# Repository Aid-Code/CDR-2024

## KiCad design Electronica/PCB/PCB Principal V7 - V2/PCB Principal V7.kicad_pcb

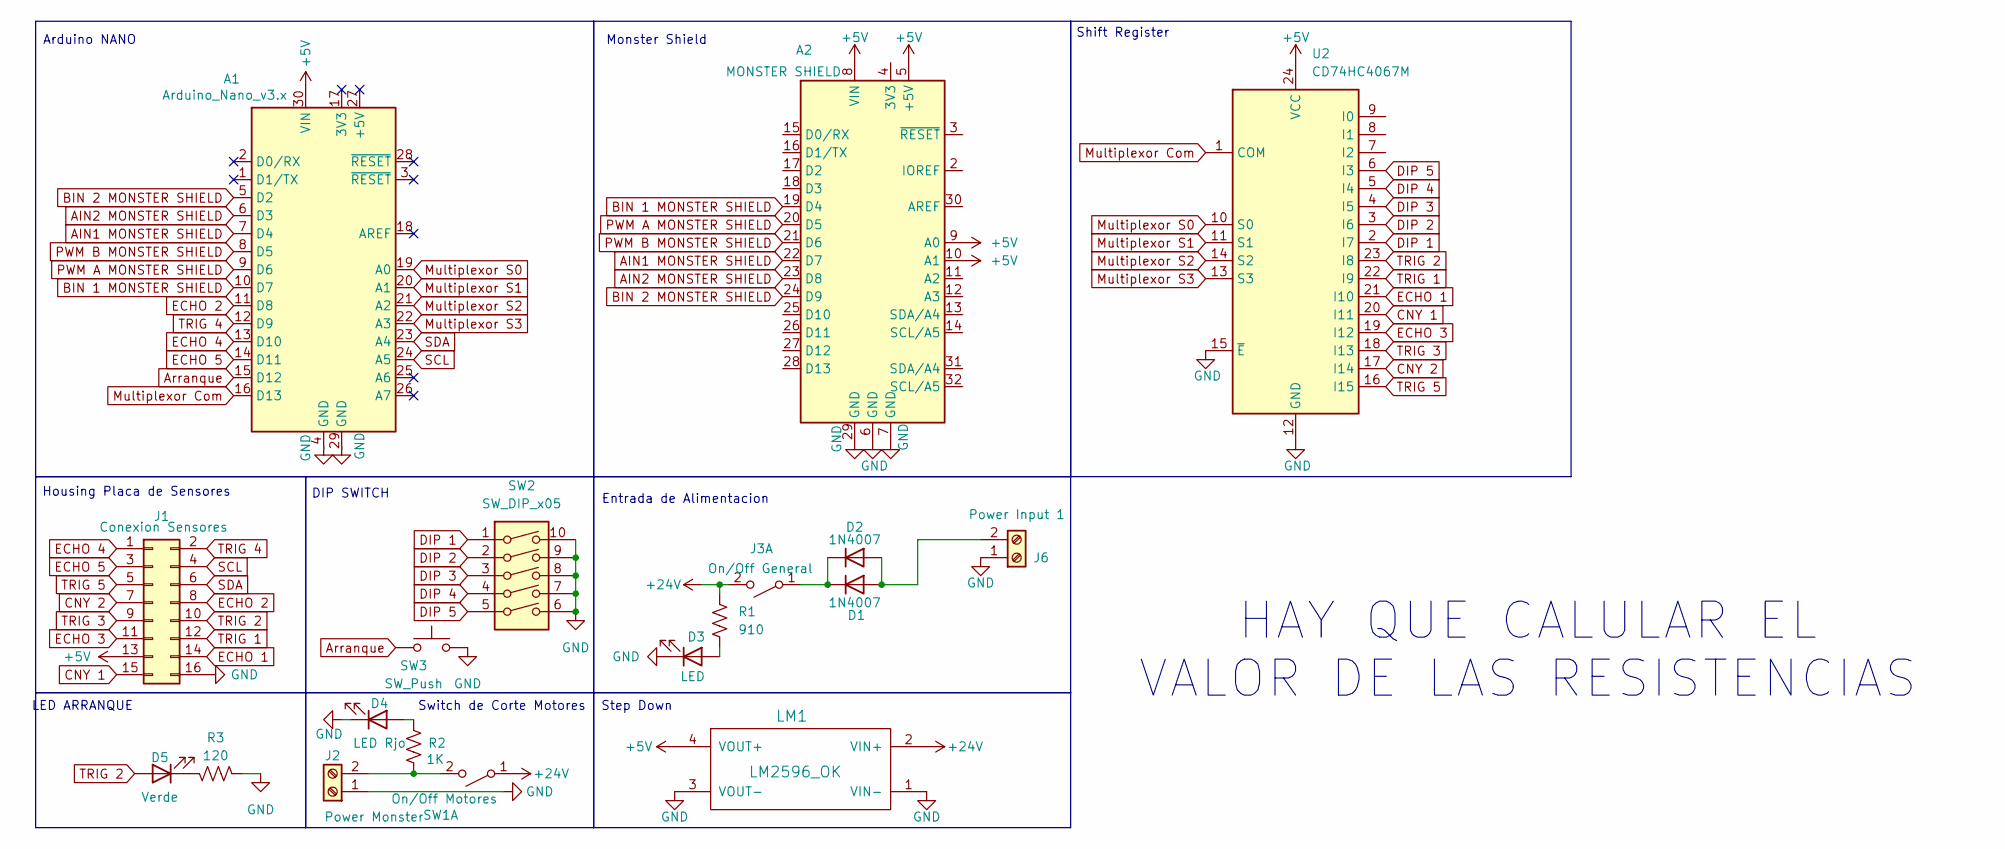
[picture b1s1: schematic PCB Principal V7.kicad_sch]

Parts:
A1: Arduino_Nano_v3.x; Arduino_Nano
A2: MONSTER SHIELD; Arduino_UNO_R3
D1, D2: 1N4007; D_DO-41_SOD81_P10.16mm_Horizontal
D3: LED; LED_D5.0mm_Horizontal_O1.27mm_Z3.0mm
D4: LED Rjo; LED_D5.0mm_Horizontal_O1.27mm_Z3.0mm
D5: Verde; LED_D5.0mm_Clear
J1: Conexion Sensores; PinHeader_2x08_P2.54mm_Horizontal
J2: Power Monster; TerminalBlock_bornier-2_P5.08mm
J3: On/Off General; TerminalBlock_bornier-2_P5.08mm
J6: Power Input 1; AMASS_XT60-M_1x02_P7.20mm_Vertical
LM1: LM2596_OK; StepDown
R1: 910; R_Axial_DIN0204_L3.6mm_D1.6mm_P7.62mm_Horizontal
R2: 1K; R_Axial_DIN0204_L3.6mm_D1.6mm_P7.62mm_Horizontal
R3: 120; R_Axial_DIN0204_L3.6mm_D1.6mm_P7.62mm_Horizontal
SW1: On/Off Motores; SW_Slide_SPDT_Angled_CK_OS102011MA1Q
SW2: SW_DIP_x05; SW_DIP_SPSTx05_Slide_9.78x14.88mm_W7.62mm_P2.54mm
SW3: SW_Push; SW_PUSH_6mm
U2: CD74HC4067M; SOIC-24W_7.5x15.4mm_P1.27mm

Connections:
+5V: A1.30 (VIN), A2.5 (+5V), A2.8 (VIN), A2.9 (A0), A2.10 (A1), J1.13, LM1.4 (VOUT+), U2.24 (VCC)
+24V: J3.2 (B), LM1.2 (VIN+), R1.1, SW1.1 (A)
AIN1 MONSTER SHIELD: A1.7 (D4), A2.22 (D7)
AIN2 MONSTER SHIELD: A1.6 (D3), A2.23 (D8)
Arranque: A1.15 (D12), SW3.1
BIN 1 MONSTER SHIELD: A1.10 (D7), A2.19 (D4)
BIN 2 MONSTER SHIELD: A1.5 (D2), A2.24 (D9)
CNY 1: J1.15, U2.20 (I11)
CNY 2: J1.7, U2.17 (I14)
DIP 1: SW2.1, U2.2 (I7)
DIP 2: SW2.2, U2.3 (I6)
DIP 3: SW2.3, U2.4 (I5)
DIP 4: SW2.4, U2.5 (I4)
DIP 5: SW2.5, U2.6 (I3)
ECHO 1: J1.14, U2.21 (I10)
ECHO 2: A1.11 (D8), J1.8
ECHO 3: J1.11, U2.19 (I12)
ECHO 4: A1.13 (D10), J1.1
ECHO 5: A1.14 (D11), J1.3
GND: A1.4 (GND), A1.29 (GND), A2.6 (GND), A2.7 (GND), A2.29 (GND), D3.1 (K), D4.1 (K), J1.16, J2.1, J6.1, LM1.1 (VIN-), LM1.3 (VOUT-), R3.2, SW2.6, SW2.7, SW2.8, SW2.9, SW2.10, SW3.2, U2.12 (GND), U2.15 (~E)
Multiplexor Com: A1.16 (D13), U2.1 (COM)
Multiplexor S0: A1.19 (A0), U2.10 (S0)
Multiplexor S1: A1.20 (A1), U2.11 (S1)
Multiplexor S2: A1.21 (A2), U2.14 (S2)
Multiplexor S3: A1.22 (A3), U2.13 (S3)
unnamed: D1.2 (A), D2.2 (A), J6.2
unnamed: D1.1 (K), D2.1 (K), J3.1 (A)
unnamed: D3.2 (A), R1.2
unnamed: D4.2 (A), R2.2
unnamed: D5.1 (K), R3.1
unnamed: J2.2, R2.1, SW1.2 (B)
PWM A MONSTER SHIELD: A1.9 (D6), A2.20 (D5)
PWM B MONSTER SHIELD: A1.8 (D5), A2.21 (D6)
SCL: A1.24 (A5), J1.4
SDA: A1.23 (A4), J1.6
TRIG 1: J1.12, U2.22 (I9)
TRIG 2: D5.2 (A), J1.10, U2.23 (I8)
TRIG 3: J1.9, U2.18 (I13)
TRIG 4: A1.12 (D9), J1.2
TRIG 5: J1.5, U2.16 (I15)

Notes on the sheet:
Switch de Corte Motores
Entrada de Alimentacion
Shift Register
LED ARRANQUE
Step Down
Housing Placa de Sensores
HAY QUE CALULAR EL VALOR DE LAS RESISTENCIAS
Monster Shield
Arduino NANO
DIP SWITCH

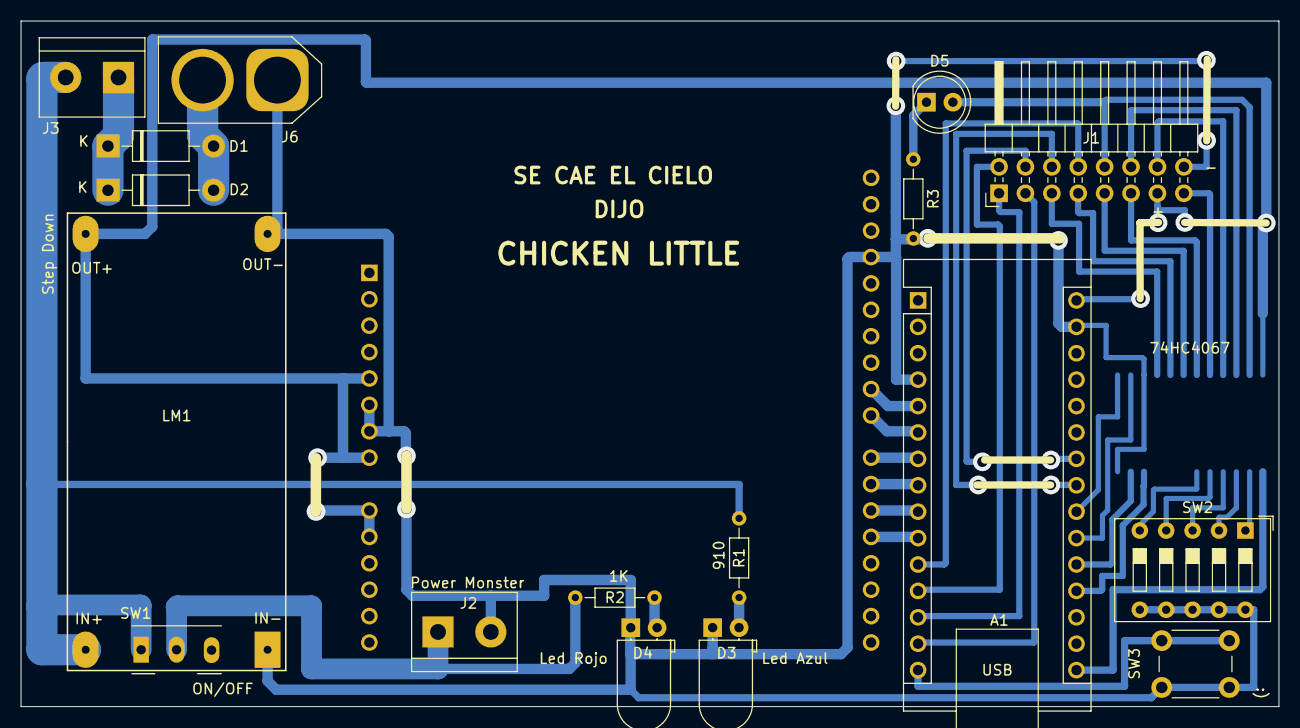
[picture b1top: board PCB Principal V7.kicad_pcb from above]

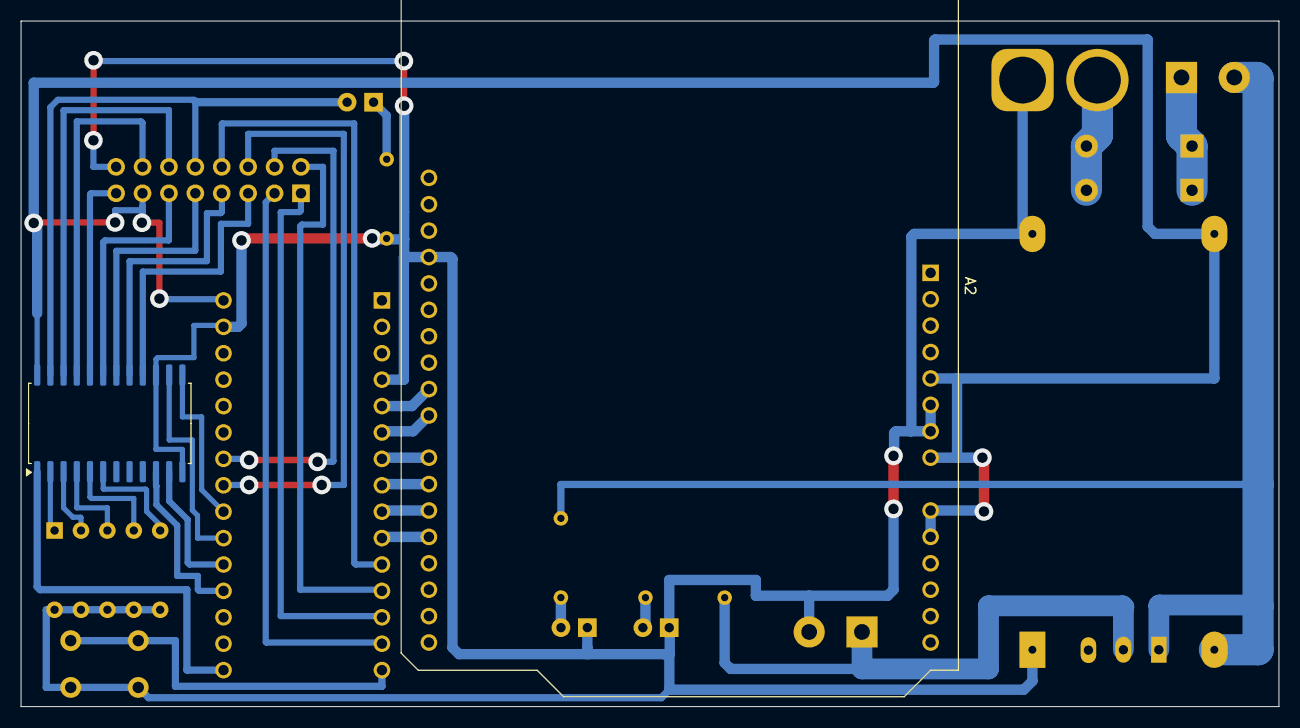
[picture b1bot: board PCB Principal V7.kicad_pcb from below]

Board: 2 copper layers, 121.0 x 65.9 mm, 19 parts (2 on the bottom side), 40 nets.

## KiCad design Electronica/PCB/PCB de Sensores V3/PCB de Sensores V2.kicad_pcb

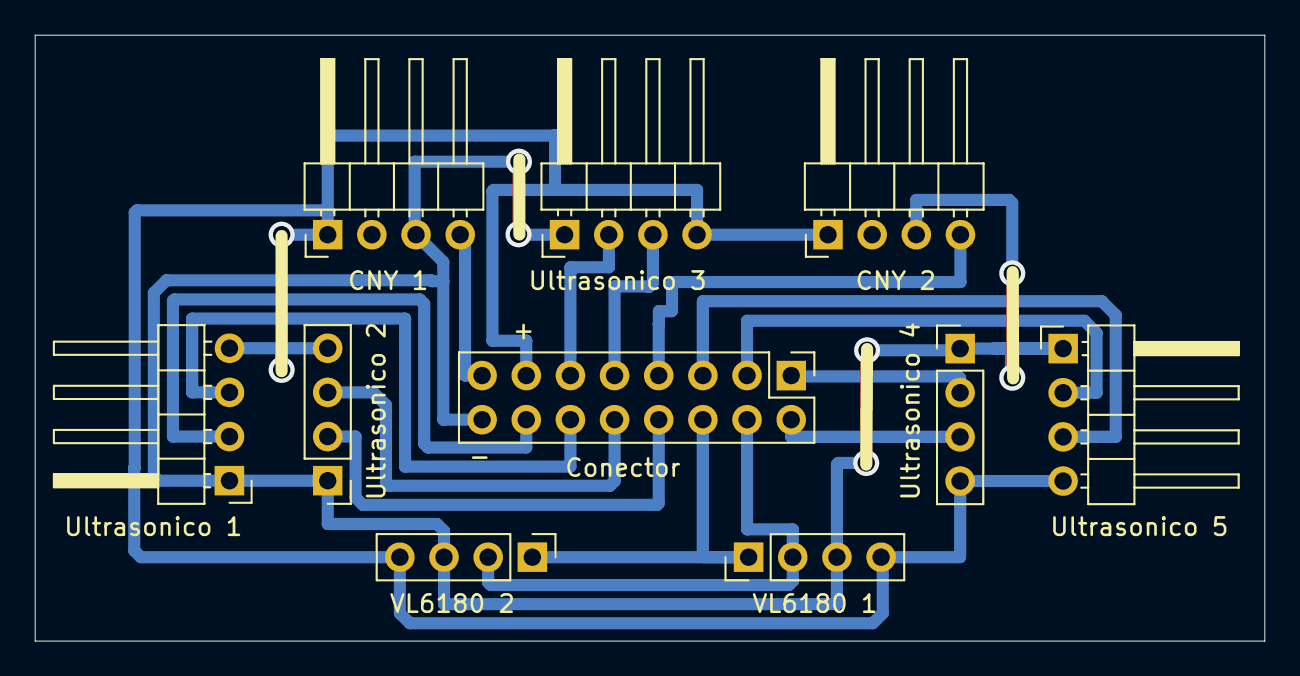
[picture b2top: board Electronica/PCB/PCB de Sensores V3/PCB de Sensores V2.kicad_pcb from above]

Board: 2 copper layers, 70.7 x 34.9 mm, 10 parts (0 on the bottom side), 16 nets.

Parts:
CNY 1: CNY1; PinHeader_1x04_P2.54mm_Horizontal
CNY 2: CNY2; PinHeader_1x04_P2.54mm_Horizontal
Conector: Conexion Sensores; PinHeader_2x08_P2.54mm_Vertical
Ultrasonico 1: ULTRASONICO1; PinHeader_1x04_P2.54mm_Horizontal
Ultrasonico 2: ULTRASONICO2; PinHeader_1x04_P2.54mm_Vertical
Ultrasonico 3: ULTRASONICO3; PinHeader_1x04_P2.54mm_Horizontal
Ultrasonico 4: ULTRASONICO4; PinHeader_1x04_P2.54mm_Vertical
Ultrasonico 5: ULTRASONICO5; PinHeader_1x04_P2.54mm_Horizontal
VL6180 1: VL6180 1; PinHeader_1x04_P2.54mm_Vertical
VL6180 2: VL6180 2; PinHeader_1x04_P2.54mm_Vertical

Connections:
+5V: CNY 1.1, CNY 2.1, Conector.13, Ultrasonico 1.4, Ultrasonico 2.4, Ultrasonico 3.4, Ultrasonico 4.4, Ultrasonico 5.4, VL6180 1.4, VL6180 2.4
CNY 1: CNY 1.4, Conector.15
CNY 2: CNY 2.4, Conector.7
ECHO 1: Conector.14, Ultrasonico 1.2
ECHO 2: Conector.8, Ultrasonico 2.2
ECHO 3: Conector.11, Ultrasonico 3.2
ECHO 4: Conector.1, Ultrasonico 4.2
ECHO 5: Conector.3, Ultrasonico 5.2
GND: CNY 1.3, CNY 2.3, Conector.16, Ultrasonico 1.1, Ultrasonico 2.1, Ultrasonico 3.1, Ultrasonico 4.1, Ultrasonico 5.1, VL6180 1.3, VL6180 2.3
SCL: Conector.4, VL6180 1.2, VL6180 2.2
SDA: Conector.6, VL6180 1.1, VL6180 2.1
TRIG 1: Conector.12, Ultrasonico 1.3
TRIG 2: Conector.10, Ultrasonico 2.3
TRIG 3: Conector.9, Ultrasonico 3.3
TRIG 4: Conector.2, Ultrasonico 4.3
TRIG 5: Conector.5, Ultrasonico 5.3

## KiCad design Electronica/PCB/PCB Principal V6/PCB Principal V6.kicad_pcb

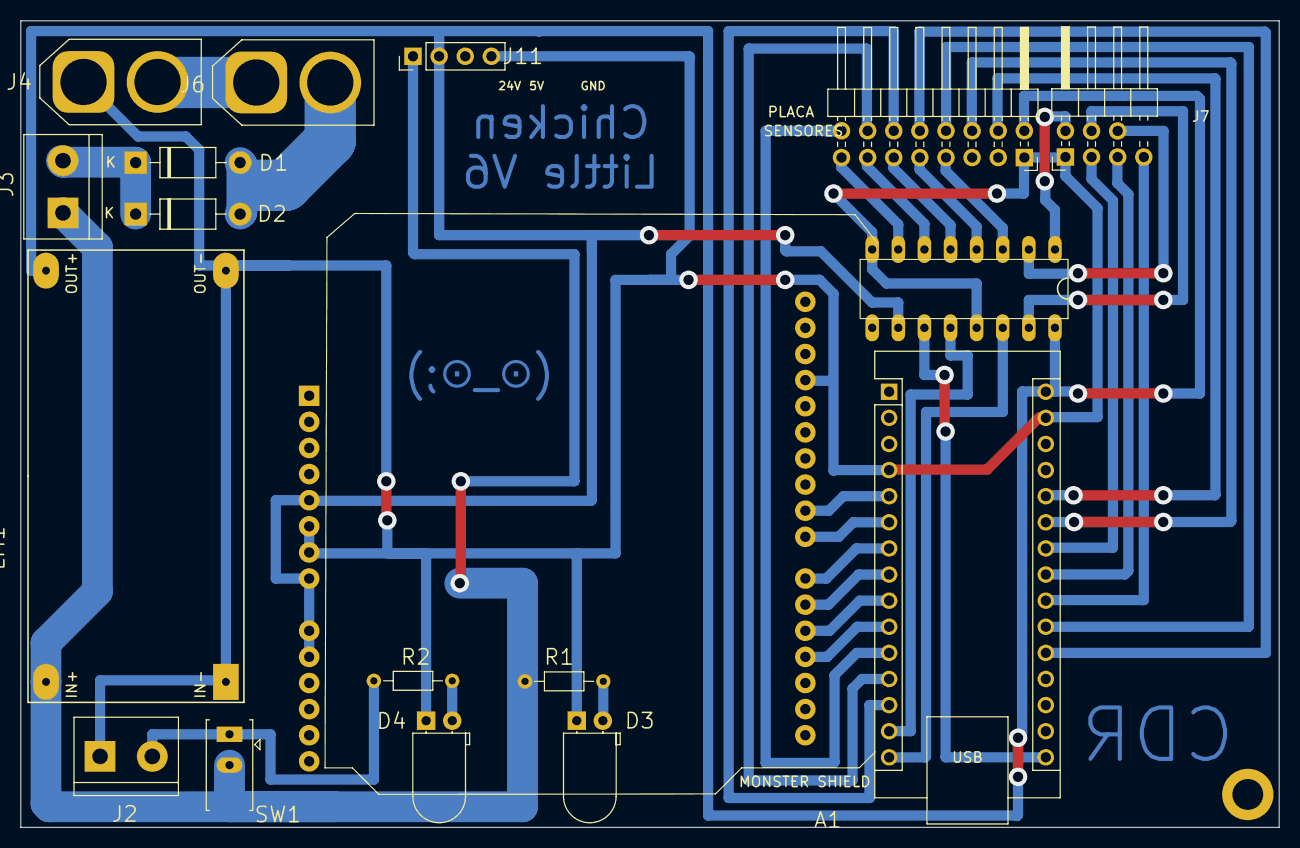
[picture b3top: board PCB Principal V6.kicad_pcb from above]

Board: 2 copper layers, 122.4 x 78.4 mm, 18 parts (1 on the bottom side), 36 nets.

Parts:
A1: Arduino_Nano_v3.x; Arduino_Nano
A2: MONSTER SHIELD; Arduino_UNO_R3
D1, D2: 1N4007; D_DO-41_SOD81_P10.16mm_Horizontal
D3, D4: LED; LED_D5.0mm_Horizontal_O1.27mm_Z3.0mm
J1: Conexion Sensores; PinHeader_2x08_P2.54mm_Horizontal
J2: Power Monster; TerminalBlock_bornier-2_P5.08mm
J3: On/Off General; TerminalBlock_bornier-2_P5.08mm
J4: Power Input 2; AMASS_XT60-M_1x02_P7.20mm_Vertical
J6: Power Input 1; AMASS_XT60-M_1x02_P7.20mm_Vertical
J7: Placa de Botones; PinHeader_2x04_P2.54mm_Horizontal
J11: Conn_01x04_Pin; PinHeader_1x04_P2.54mm_Vertical
LM1: LM2596_OK; StepDown
R1, R2: 220; R_Axial_DIN0204_L3.6mm_D1.6mm_P7.62mm_Horizontal
SW1: On/Off Motores; SW_Slide_SPDT_Straight_CK_OS102011MS2Q
U1: 74HC595; DIP16-2.54-20.32X5.84MM

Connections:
+5V: A1.30 (VIN), A2.5 (+5V), A2.8 (VIN), A2.9 (A0), A2.10 (A1), J1.15, J11.2, LM1.4 (VOUT+), U1.10 (~SRCLR), U1.16 (VCC)
+24V: J3.1 (A), J11.1, LM1.2 (VIN+), R1.1, SW1.2 (B)
AIN1 MONSTER SHIELD: A1.7 (D4), A2.22 (D7)
AIN2 MONSTER SHIELD: A1.6 (D3), A2.23 (D8)
BIN 1 MONSTER SHIELD: A1.10 (D7), A2.19 (D4)
BIN 2 MONSTER SHIELD: A1.5 (D2), A2.24 (D9)
BTN1: A1.23 (A4), J7.5
BTN2: A1.24 (A5), J7.3
CNY 1: A1.26 (A7), J1.13
CNY 2: A1.25 (A6), J1.11
Clock: A1.16 (D13), U1.11 (SRCLK)
Data: A1.15 (D12), U1.14 (SER)
ECHO 1: A1.11 (D8), J1.1
ECHO 2: A1.12 (D9), J1.3
ECHO 3: A1.13 (D10), J1.5
ECHO 4: A1.20 (A1), J1.7
ECHO 5: A1.21 (A2), J1.9
GND: A1.4 (GND), A1.29 (GND), A2.6 (GND), A2.7 (GND), A2.29 (GND), D3.1 (K), D4.1 (K), J1.16, J2.1, J4.1, J7.1, J11.4, LM1.1 (VIN-), LM1.3 (VOUT-), U1.8 (GND), U1.13 (~OE)
LED1: A1.22 (A3), J7.7
LED2: J7.2, U1.1 (QB)
LED3: J7.4, U1.15 (QA)
LED4: J7.6, U1.2 (QC)
Latch: A1.14 (D11), U1.12 (RCLK)
unnamed: D1.2 (A), D2.2 (A), J6.2
unnamed: D1.1 (K), D2.1 (K), J3.2 (B)
unnamed: D3.2 (A), R1.2
unnamed: D4.2 (A), R2.2
unnamed: J2.2, R2.1, SW1.1 (A)
unnamed: J4.2, J6.1
PWM A MONSTER SHIELD: A1.9 (D6), A2.20 (D5)
PWM B MONSTER SHIELD: A1.8 (D5), A2.21 (D6)
TRIG 1: J1.10, U1.3 (QD)
TRIG 2: J1.2, U1.7 (QH)
TRIG 3: J1.4, U1.6 (QG)
TRIG 4: J1.8, U1.4 (QE)
TRIG 5: J1.6, U1.5 (QF)

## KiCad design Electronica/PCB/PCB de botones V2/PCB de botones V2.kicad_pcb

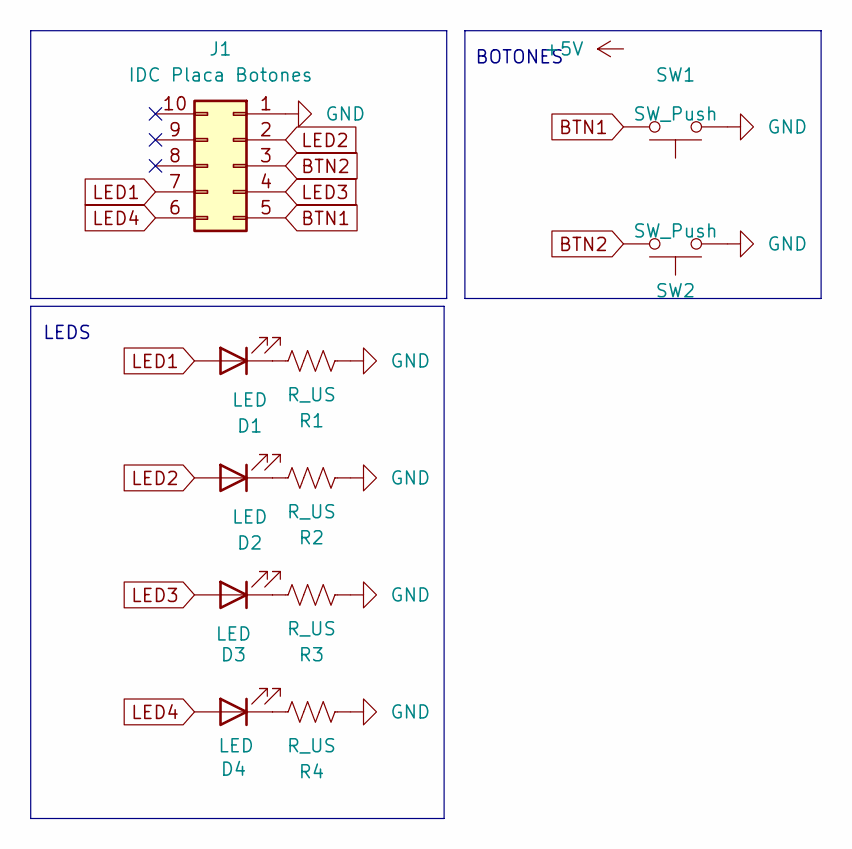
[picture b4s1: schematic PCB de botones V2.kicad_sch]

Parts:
D1, D2, D3, D4: LED; LED_D5.0mm
J1: IDC Placa Botones; IDC-Header_2x05_P2.54mm_Horizontal
R1, R2, R3, R4: R_US; R_Axial_DIN0207_L6.3mm_D2.5mm_P10.16mm_Horizontal
SW1, SW2: SW_Push; SW_PUSH_6mm

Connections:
BTN1: J1.5, SW1.1
BTN2: J1.3, SW2.1
GND: J1.1, R1.1, R2.1, R3.1, R4.1, SW1.2, SW2.2
LED1: D1.2 (A), J1.7
LED2: D2.2 (A), J1.2
LED3: D3.2 (A), J1.4
LED4: D4.2 (A), J1.6
unnamed: D1.1 (K), R1.2
unnamed: D2.1 (K), R2.2
unnamed: D3.1 (K), R3.2
unnamed: D4.1 (K), R4.2

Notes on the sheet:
LEDS
BOTONES

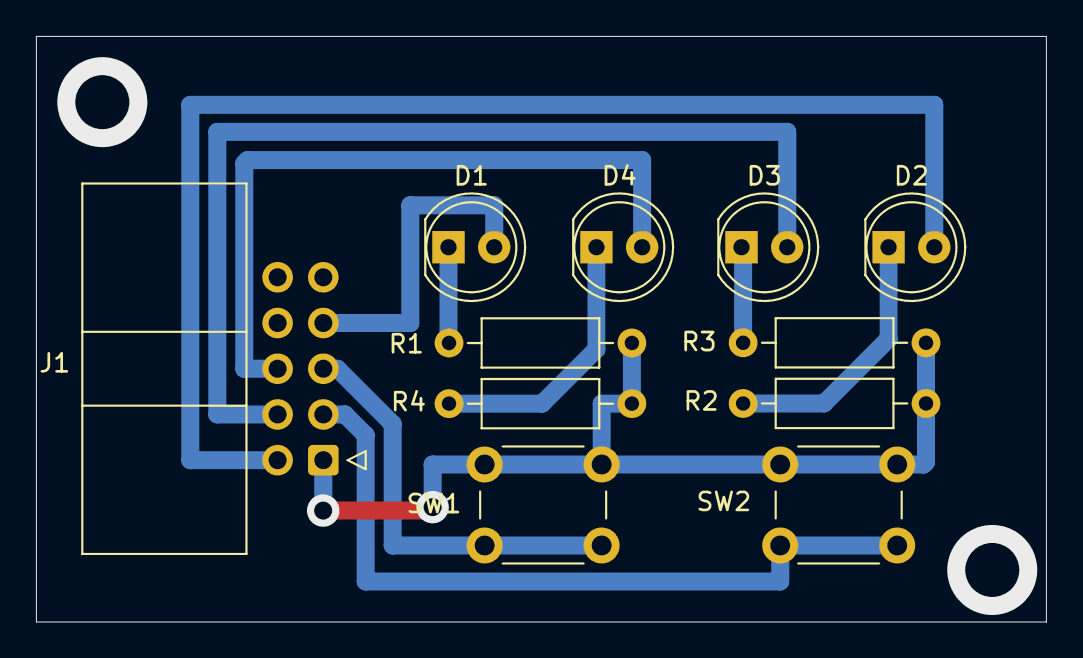
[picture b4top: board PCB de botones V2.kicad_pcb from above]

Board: 2 copper layers, 56.1 x 32.5 mm, 11 parts (0 on the bottom side), 11 nets.

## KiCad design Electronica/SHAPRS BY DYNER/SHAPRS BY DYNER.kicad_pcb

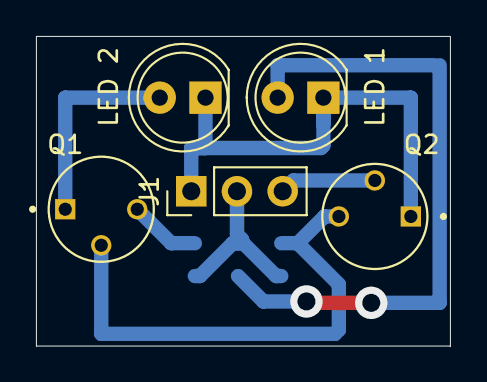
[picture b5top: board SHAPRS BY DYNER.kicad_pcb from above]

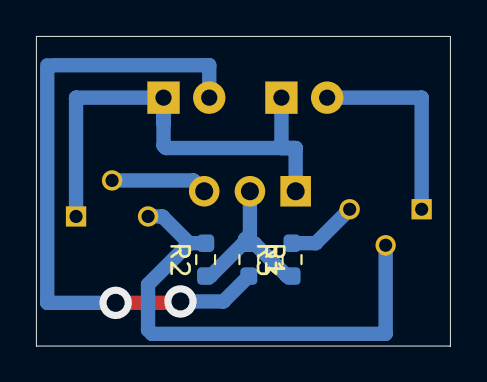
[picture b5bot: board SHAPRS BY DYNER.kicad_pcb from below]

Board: 2 copper layers, 23.0 x 17.2 mm, 8 parts (3 on the bottom side), 7 nets.

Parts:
J1: Conn_01x03_Socket; PinHeader_1x03_P2.54mm_Vertical
LED 1, LED 2: LED; LED_D5.0mm
Q1, Q2: 2N2222A; TO127P584H533-3
R1, R2, R3: 330; R_0603_1608Metric_Pad0.98x0.95mm_HandSolder

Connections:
+5V: J1.2, R1.1, R2.1, R3.1
GND: J1.1, LED 1.1 (K), LED 2.1 (K), Q2.1
unnamed: LED 1.2 (A), R1.2
unnamed: LED 2.2 (A), Q1.1
unnamed: Q1.2, Q2.3, R2.2
unnamed: Q1.3, R3.2
pin: J1.3, Q2.2

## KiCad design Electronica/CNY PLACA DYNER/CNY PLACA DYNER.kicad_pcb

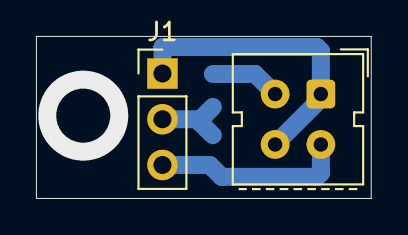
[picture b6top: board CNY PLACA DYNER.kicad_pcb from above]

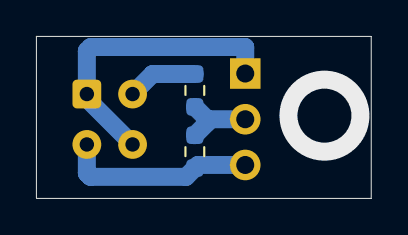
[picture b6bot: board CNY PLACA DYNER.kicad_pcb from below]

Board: 2 copper layers, 18.6 x 9.0 mm, 4 parts (2 on the bottom side), 4 nets.

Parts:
J1: Conn_01x03_Socket; PinHeader_1x03_P2.54mm_Vertical
R1: 220; R_0603_1608Metric_Pad0.98x0.95mm_HandSolder
R2: 10k; R_0603_1608Metric_Pad0.98x0.95mm_HandSolder
U1: CNY70; Vishay_CNY70

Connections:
+5V: J1.1, U1.1 (A), U1.3 (C)
CNY: J1.3, R2.1, U1.4 (E)
GND: J1.2, R1.1, R2.2
unnamed: R1.2, U1.2 (K)

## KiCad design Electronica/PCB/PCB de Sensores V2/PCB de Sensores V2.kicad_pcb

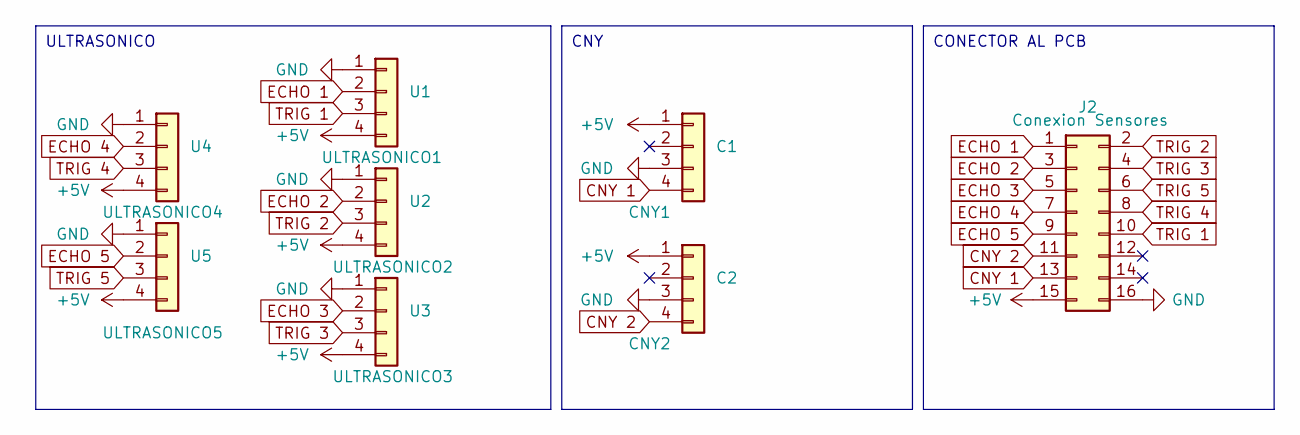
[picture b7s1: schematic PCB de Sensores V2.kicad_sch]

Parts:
C1: CNY1; PinHeader_1x04_P2.54mm_Horizontal
C2: CNY2; PinHeader_1x04_P2.54mm_Horizontal
J2: Conexion Sensores; PinHeader_2x08_P2.54mm_Vertical
U1: ULTRASONICO1; PinHeader_1x04_P2.54mm_Horizontal
U2: ULTRASONICO2; PinHeader_1x04_P2.54mm_Vertical
U3: ULTRASONICO3; PinHeader_1x04_P2.54mm_Horizontal
U4: ULTRASONICO4; PinHeader_1x04_P2.54mm_Vertical
U5: ULTRASONICO5; PinHeader_1x04_P2.54mm_Horizontal

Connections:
+5V: C1.1, C2.1, J2.15, U1.4, U2.4, U3.4, U4.4, U5.4
CNY 1: C1.4, J2.13
CNY 2: C2.4, J2.11
ECHO 1: J2.1, U1.2
ECHO 2: J2.3, U2.2
ECHO 3: J2.5, U3.2
ECHO 4: J2.7, U4.2
ECHO 5: J2.9, U5.2
GND: C1.3, C2.3, J2.16, U1.1, U2.1, U3.1, U4.1, U5.1
TRIG 1: J2.10, U1.3
TRIG 2: J2.2, U2.3
TRIG 3: J2.4, U3.3
TRIG 4: J2.8, U4.3
TRIG 5: J2.6, U5.3

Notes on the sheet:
CONECTOR AL PCB
ULTRASONICO
CNY

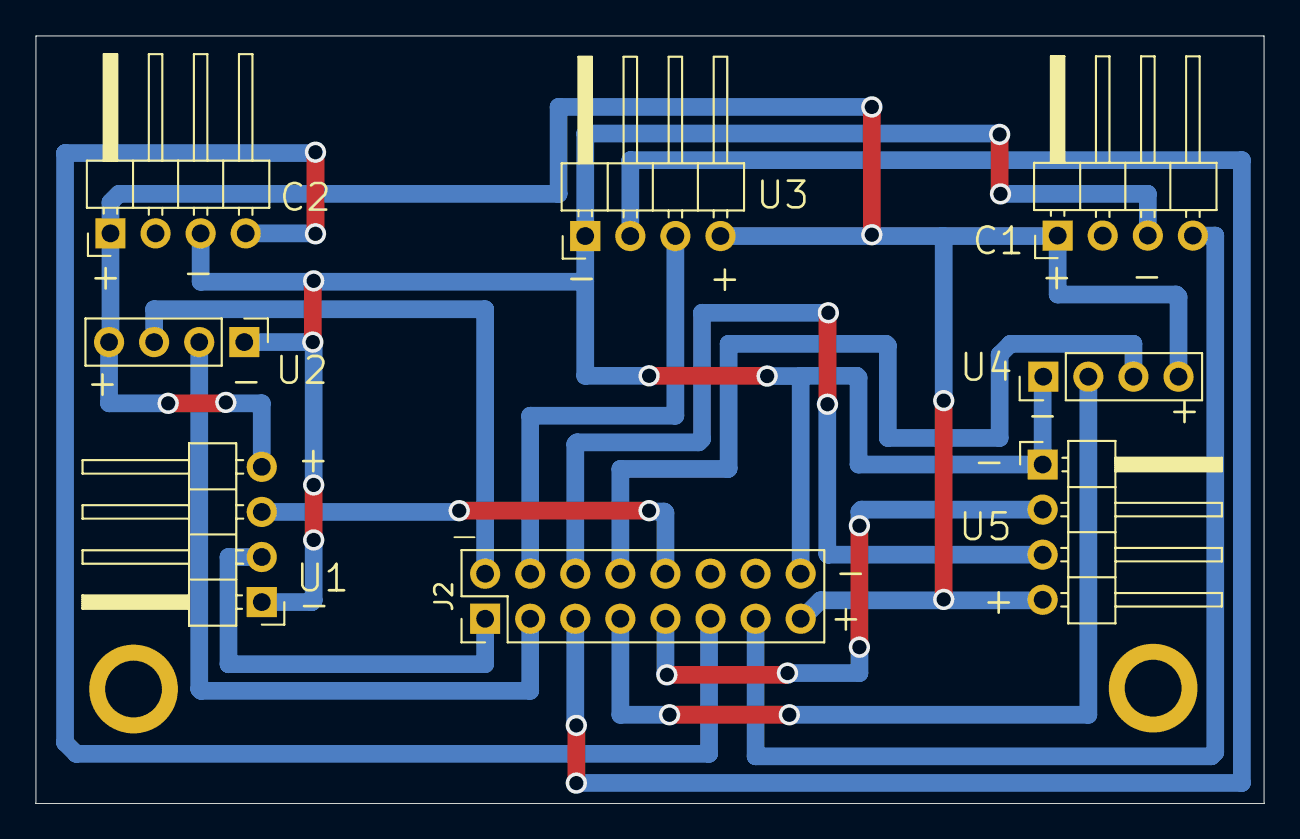
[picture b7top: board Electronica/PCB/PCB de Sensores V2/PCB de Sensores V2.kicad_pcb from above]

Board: 2 copper layers, 69.2 x 43.3 mm, 8 parts (0 on the bottom side), 14 nets.

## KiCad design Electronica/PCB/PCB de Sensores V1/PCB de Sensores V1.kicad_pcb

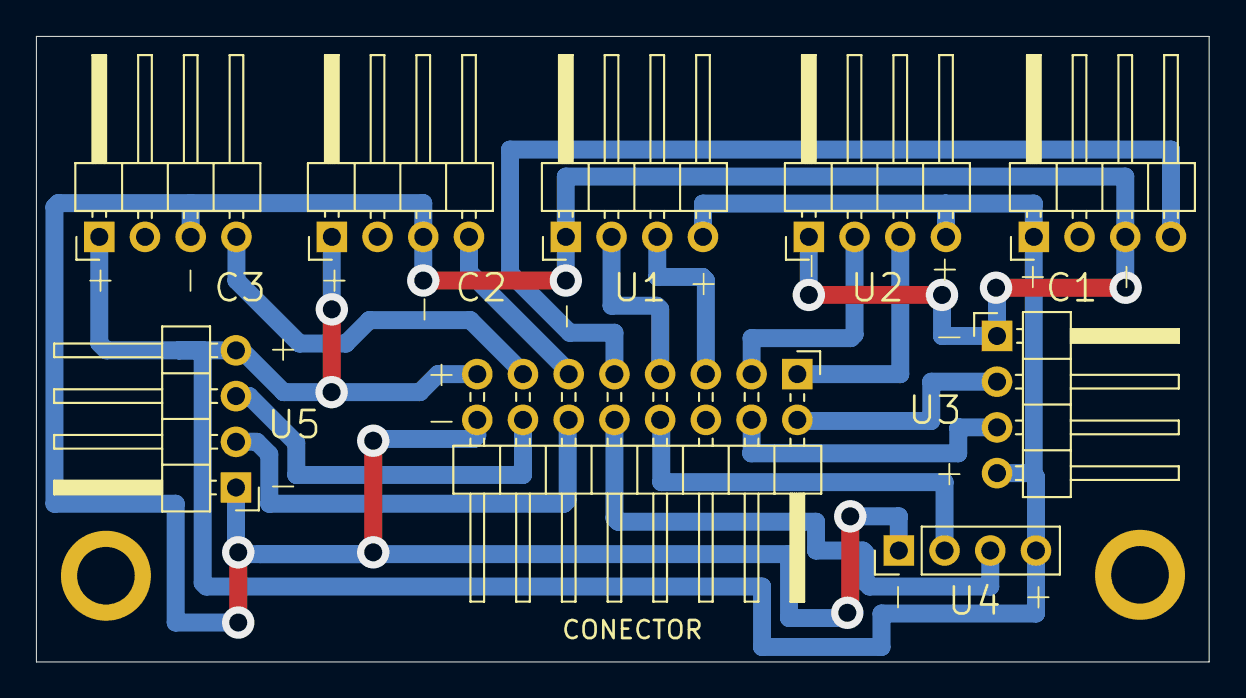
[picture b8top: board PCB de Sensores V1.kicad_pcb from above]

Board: 2 copper layers, 65.2 x 34.7 mm, 9 parts (0 on the bottom side), 15 nets.

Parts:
C1: CNY1; PinHeader_1x04_P2.54mm_Horizontal
C2: CNY2; PinHeader_1x04_P2.54mm_Horizontal
C3: CNY3; PinHeader_1x04_P2.54mm_Horizontal
CONECTOR: Conexion Sensores; PinHeader_2x08_P2.54mm_Horizontal
U1: ULTRASONICO1; PinHeader_1x04_P2.54mm_Horizontal
U2: ULTRASONICO2; PinHeader_1x04_P2.54mm_Horizontal
U3: ULTRASONICO3; PinHeader_1x04_P2.54mm_Horizontal
U4: ULTRASONICO4; PinHeader_1x04_P2.54mm_Vertical
U5: ULTRASONICO5; PinHeader_1x04_P2.54mm_Horizontal

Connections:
+5V: C1.1, C2.1, C3.1, CONECTOR.15, U1.4, U2.4, U3.4, U4.4, U5.4
CNY 1: C1.4, CONECTOR.9
CNY 2: C2.4, CONECTOR.11
CNY 3: C3.4, CONECTOR.13
ECHO 1: CONECTOR.7, U1.2
ECHO 2: CONECTOR.3, U2.2
ECHO 3: CONECTOR.2, U3.2
ECHO 4: CONECTOR.8, U4.2
ECHO 5: CONECTOR.12, U5.2
GND: C1.3, C2.3, C3.3, CONECTOR.16, U1.1, U2.1, U3.1, U4.1, U5.1
TRIG 1: CONECTOR.5, U1.3
TRIG 2: CONECTOR.1, U2.3
TRIG 3: CONECTOR.4, U3.3
TRIG 4: CONECTOR.10, U4.3
TRIG 5: CONECTOR.14, U5.3

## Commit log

2023-06-07 Diseño Estructura Robotito 1
    - Versiones de estructura
    - Diseño de estructura "definitiva" (con sensores, soporte de sensores)
    - Archivo ensamblaje motor
    - Diseños de "soporte" de motores (de prueba)
2023-06-09 mover objetos
2024-04-26 Carpetas de division
2024-04-26 1° Prueba
2024-04-27 hc-04 diseño
2024-04-27 same antes
2024-04-28 PCB esquematico sin terminar faltan los step up y step down
2024-04-29 Inicio de diseño del pcb
2024-05-02 Esquematico correjido por prieto solo falta el step up y step down
2024-05-02 Esquematico terminado y esquemas del step down y step up
2024-05-03 EL BETO CON HC
2024-05-03 Actualizacion
2024-05-03 Dyner te la comes
2024-05-03 Huella step Down
2024-05-07 El beto buen diseño faltan componentes
2024-05-08 diseños
2024-05-09 dfdsgh
2024-05-10 BET es el BUENO!!
2024-05-10 EL BET ES EL BUENOO
2024-05-10 BET ES EL BUENO
2024-05-10 No se
2024-05-10 Quedan 4 puentes
2024-05-10 Sportes ultasonico
2024-05-10 4 puentes
2024-05-10 Codigo - Falta
2024-05-10 electronica
2024-05-13 tapa
2024-05-13 Separar base y cuerpo
2024-05-13 qwert
2024-05-14 EL BETO COMPLETO V1 Y ORGANIZACION
2024-05-14 AIDEN TE MATO
2024-05-14 PARTES DEL BETO
2024-05-14 Placa hoy le pregunto a prieto del diseño
2024-05-15 RAMPA CON SOPORTE Y TODO DIVIDIDO
2024-05-17 Pcb En teoria Terminada y verificada por Prieto
2024-05-24 Me quiero cortar las bolas
2024-05-25 Placa corregida sin placa de botones
2024-05-26 PCB de botones
2024-05-31 PCB Botones
2024-06-03 PCB DE VOTONES
2024-06-03 Pcb botones con arreglos de distancias
2024-06-03 PCB de botones terminada
2024-06-03 Placa de leds en 3d
2024-06-05 diseño terminado
2024-06-07 vias pcb botones
2024-06-11 ruedas
2024-06-13 Pcb el beto v2
2024-06-14 Pcb terminada
2024-06-14 Motores funcionan, sensores funcionan
2024-06-25 diseño OP
2024-07-08 Motores funcionando, no funciona con ultrasonicos
2024-07-10 Prueba completo (sin probar) estrategias a media
2024-07-12 Pruebas completas (con fuente)
    CNY izquierdo funcionando
    Ultrasonicos con motores funcionando
2024-07-15 terminandooo
2024-07-16 TERMINADO
    MOLDES TERMINADO
    BASE TERMINADA
    CUERPO TERMINADO
    TECHO 1 TERMINADO
    TECHO 2 TERMINADO
2024-07-30 Pruebas
2024-08-01 CNYs Funcionando
2024-08-02 Robot funcionando. Ultrasonicos dudosos
2024-08-03 ITBA 2024
2024-08-03 PCB sensores
2024-08-03 Nuevo diseño
2024-08-03 Diseños con motores
2024-08-04 Ensamblajes con componentes
    PARANA NOS VEMOS
2024-08-04 Esquematico PCB V4 terminado
2024-08-04 PCB Principal TERMINADA
2024-08-04 Diseno casi terminado
2024-08-04 PCB Sensores a modificar
2024-08-04 SELIGRAFIA
2024-08-04 aiden tonto
2024-08-05 pcb de leds
2024-08-05 botones
2024-08-05 PDF SENSORES
2024-08-05 Listo PCB Botones
2024-08-05 diseno 3/4
2024-08-05 PCB Principal con leds
2024-08-05 Step pcb principal
2024-08-05 placa de botones en diseno
2024-08-05 TEST POINTSSSS
2024-08-05 soporte ultrasonico prueba
2024-08-05 V4 DE RUNDELL
2024-08-05 Codigo nuevo sin terminar
2024-08-06 spoprtes
2024-08-06 DISEñO TERMIADOOO
2024-08-06 TERMINADO
2024-08-07 pcb sensores corregida
    Tonto el que lee
2024-08-10 medidas motores
2024-08-14 PCB Principal V5 (sin terminar)
2024-08-14 Codigo principal (en proceso)
2024-08-16 nada
2024-08-20 PCB V6
2024-08-20 PCB CHERNIAK TERMINAR
    TONTO EL QUE LEE
2024-08-21 pcb terminar?
    TONTO EL QUE LEE
2024-08-21 Diseño 3d modi
2024-08-21 TERMINACION
    -Placa Principal
    -Techo de 60 Grados
    -Techo Tapa
2024-08-22 TERMINADO V7
2024-08-22 Serigrafia placa principal
2024-08-26 Techo de 60 nuevo
2024-08-28 CODIGO TERMIANADO Y FUNCIONA, PLACA V6 TERMINADA
2024-08-29 Placa sensores y placa principar terminada
2024-08-29 PCB V6 ACTUALIZADA
2024-08-30 CUERPO CON 5 ULTRASONICOS
2024-08-30 pcb principal v7 sin terminar
2024-08-30 Codigo en proceso
2024-08-30 codigo nuevo
2024-08-30 codigo con agus
2024-08-30 coadaigo con agus
2024-08-30 PCB sensores v2 y principal v7 terminadas
2024-08-30 CODIGO BOTONESS PORR TERMINAR
2024-08-30 techo de 60 y cuerpo con 5 ultrasonicos
2024-08-30 diseño V9 terminado
2024-08-30 v9 termiado
2024-08-30 botones por dyner (a chequear)
2024-08-30 nose como se hace el sketch main
2024-08-31 codigo arreglado
2024-08-31 Homologado!
2024-09-01 PROBAR QUE ONDA EL CODIGO
2024-09-02 placa botones y codigo
2024-09-02 placas
    Seligrafis y capa inferior de:
    Botones v2
    Sensores v2
    Principal v7
2024-09-02 orden leds
2024-09-02 Comentarios codigo dyner a probar
2024-09-03 tuercas
2024-09-03 prieto toco
2024-09-04 PLACA DE CNY Y INFRAROJO
2024-09-06 Codigo
2024-09-06 codigo con prieto
2024-09-09 PCB V5 LINDA HERMOSA DIVINA
2024-09-09 PCB Principal V5 terminada
2024-09-09 SERIGRTAFIA
2024-09-09 seligrafiaskfbvlajBSJFV
    TONTO EL Q LEE
2024-09-11 5 SENSORES
2024-09-11 prueba de botones, contador binario
2024-09-12 prueba shift register
2024-09-12 pruebas shift register
2024-09-15 Parana 2024
    - Sumo funcionando TODO con 3 ultrasonicos y 2 cny (Codigo de prueba completo con shift register)
    - Rango ultrasonicos en > 40cm
    - PWM 255 cuando ve
    - PWM 100 cuando no ve
    - PWM 250 cuando ve linea blanca
    - Codigo de contador en binario funcionando
2024-09-15 COSAS PARA MEJORAR
2024-09-16 Cosas para mejorar edicion micro
2024-09-16 STRATS
2024-09-16 NUEVAS REUDAS
2024-09-16 ruedas nuevas y cuerpo 5
2024-09-16 tonot
2024-09-18 Ni idea que hice
2024-09-23 llanta modles
2024-09-26 Maquina seteadora en proceso
2024-09-26 Super antirrebote
2024-09-27 dfhdhf
2024-09-30 llanta new
2024-10-01 Cosas ordenadas
2024-10-10 pwm chill 70
2024-10-19 CODIGO CON ESTRATEGIAS BABY
2024-10-21 Hurlingham 2024
    La verdad no recuerdo que hice, nada muy significativo.
    Calibre los cny, puli las estrategias, hice que el modo radar se mueva siempre para la derecha si no ve nada (HAY QUE MODIFICAR ESO) pero fue para evitar que nos metan falta si no se movia a los 5 se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
2024-10-24 ANTES de tictac y direcciones de arranque
2024-10-24 Codigo hermoso bello precioso
    Estrategias nuevas o modificadas:
    - Tictac (va girando levemente de un lado al otro hasta que ve algo)
    - Radar (sigue al oponente)
    NUEVO:
    - Direcciones (se puede arrancar para el lado que se determine)
    - Deteccion de ambos CNYs a la vez, reaccion distinta a que si se detecta unicamente uno
2024-10-24 Cambio de IDE
2024-10-24 nada interesante por aqui
2024-10-28 UTN 2024
    Principalmente agregue las direcciones de giro por grados
2024-10-28 Antes de hacer 5 sensores
2024-10-28 Muchas cosas
2024-10-29 nuevos soportes y cuerpo de 5 sensores
2024-10-29 Agarres tuercas
2024-10-29 Redondeo ultrasonicos
2024-10-30 Agregar el STL
2024-11-02 emm codigo con 5 sensores sin probar y con pwm en funciones de movimiento
2024-11-07 no se que carajo hice aca
2024-11-07 pre bahia
2024-11-09 bahia deluxe (pre competencia)
2024-11-11 Bahia Blanca
    - Sin 5 sensores
    - Radar funciona lindo (pero se queda quieto)
    - Tic tac se buguea
    - Pasitos divino
2024-11-18 soportes
2024-11-29 umbral cny nuevo
2025-02-19 Falta terminar
2025-02-19 V7-V2 terminada
2025-02-19 V7-V2 TERMINADISIMA
2025-02-19 Sensores V3
2025-02-19 Placa principal terminada
2025-02-20 Principal erminada
2025-02-20 terminava v7
2025-02-20 teminada
2025-02-20 Actualizar modelos 3D
2025-02-20 Modelos 3D hechos
2025-02-25 Subir los .Step
2025-02-25 Serigrafia
2025-02-25 Tofo a fusion
2025-02-26 codigo cpp y h
